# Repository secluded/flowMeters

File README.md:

# flowMeters

A pulse counting shield for the iTead IBoard Pro.
Debounces pusles for upto 32 meters and reports each pulse to a server.
Uses ethernet/mqtt.
Saves to an SD Card if it cannot contact server.

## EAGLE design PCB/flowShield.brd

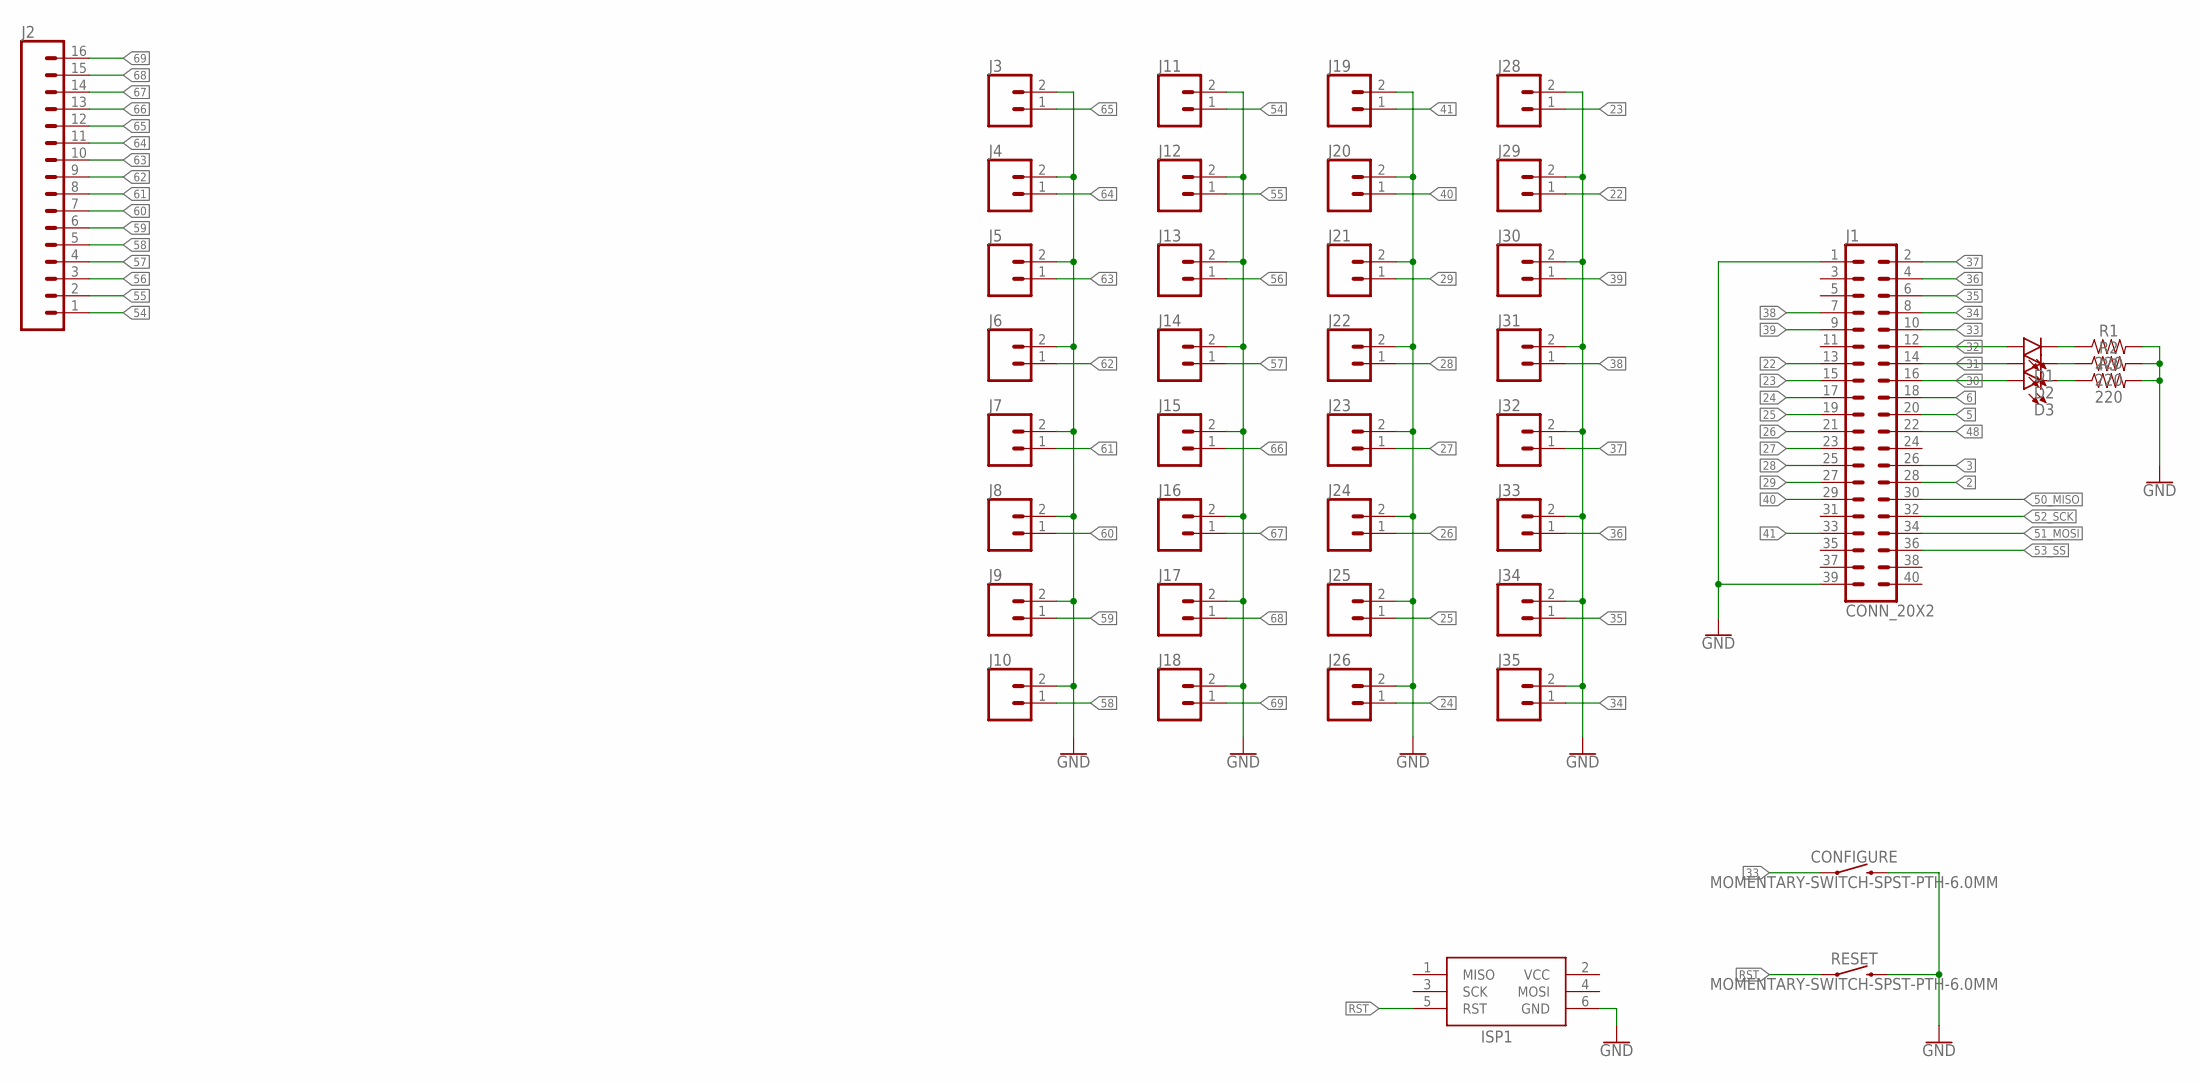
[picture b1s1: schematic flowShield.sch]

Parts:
CONFIGURE: MOMENTARY-SWITCH-SPST-PTH-6.0MM; TACTILE_SWITCH_PTH_6.0MM
D1, D2, D3: LED3MM; LED_3MM
ISP1: ADAFRUIT_AVRISP-6; ADAFRUIT_AVRISP
J1: CONN_20X2; 2X20
J2: CONN_16; 1X16
J3, J4, J5, J6, J7, J8, J9, J10, J11, J12, J13, J14, J15, J16, J17, J18, J19, J20, J21, J22, J23, J24, J25, J26, J28, J29, J30, J31, J32, J33, J34, J35: CONN_025MM; SCREWTERMINAL-5MM-2
R1, R2, R3: 220; AXIAL-0.3
RESET: MOMENTARY-SWITCH-SPST-PTH-6.0MM; TACTILE_SWITCH_PTH_6.0MM

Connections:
2: J1.28
3: J1.26
5: J1.20
6: J1.18
22: J1.13, J29.1
23: J1.15, J28.1
24: J1.17, J26.1
25: J1.19, J25.1
26: J1.21, J24.1
27: J1.23, J23.1
28: J1.25, J22.1
29: J1.27, J21.1
30: D3.A, J1.16
31: D2.A, J1.14
32: D1.A, J1.12
33: CONFIGURE.1, J1.10
34: J1.8, J35.1
35: J1.6, J34.1
36: J1.4, J33.1
37: J1.2, J32.1
38: J1.7, J31.1
39: J1.9, J30.1
40: J1.29, J20.1
41: J1.33, J19.1
48: J1.22
50_MISO: J1.30
51_MOSI: J1.34
52_SCK: J1.32
53_SS: J1.36
54: J2.1, J11.1
55: J2.2, J12.1
56: J2.3, J13.1
57: J2.4, J14.1
58: J2.5, J10.1
59: J2.6, J9.1
60: J2.7, J8.1
61: J2.8, J7.1
62: J2.9, J6.1
63: J2.10, J5.1
64: J2.11, J4.1
65: J2.12, J3.1
66: J2.13, J15.1
67: J2.14, J16.1
68: J2.15, J17.1
69: J2.16, J18.1
GND: CONFIGURE.3 (2), ISP1.6 (GND), J1.1, J1.39, J3.2, J4.2, J5.2, J6.2, J7.2, J8.2, J9.2, J10.2, J11.2, J12.2, J13.2, J14.2, J15.2, J16.2, J17.2, J18.2, J19.2, J20.2, J21.2, J22.2, J23.2, J24.2, J25.2, J26.2, J28.2, J29.2, J30.2, J31.2, J32.2, J33.2, J34.2, J35.2, R1.P$2 (2), R2.P$2 (2), R3.P$2 (2), RESET.3 (2)
unnamed: D1.K (C), R1.P$1 (1)
unnamed: D2.K (C), R2.P$1 (1)
unnamed: D3.K (C), R3.P$1 (1)
RST: ISP1.5 (RST), RESET.1
VCC: ISP1.2 (VCC)

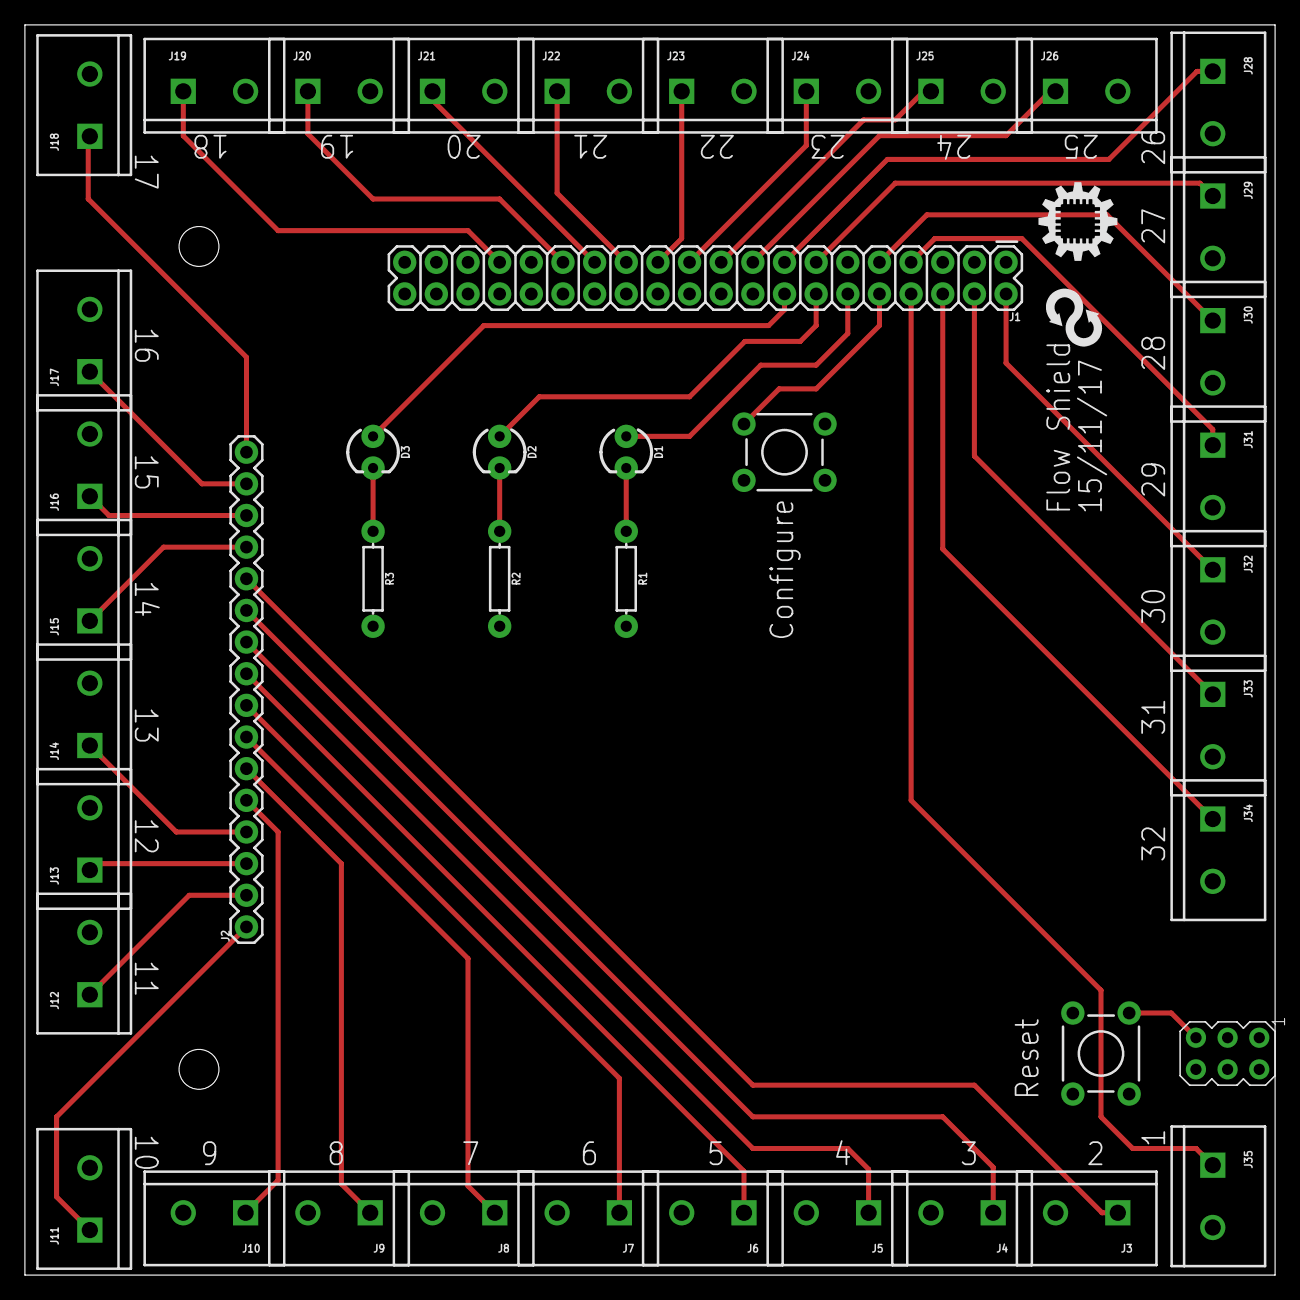
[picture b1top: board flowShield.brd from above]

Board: 2 copper layers, 100.3 x 100.3 mm, 45 parts (0 on the bottom side), 41 nets.

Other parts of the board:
U$1: ID_LOGO_X0.25
U$12: REFACTORLOOP

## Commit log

2017-12-21 Added in Leds, Pin defines, Some basic error handling & indication

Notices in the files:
parts and their libraries:
SparkFun-Connectors: Licensing: Creative Commons ShareAlike 4.0 International - https://creativecommons.org/licenses/by-sa/4.0
